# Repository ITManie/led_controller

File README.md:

# 

Arduino project to control RGB LED strip

## Part list
 - IQRF Development set [IQRF DS-START-04](http://eshop.iqrf.org/products/detail/DS-START-04)
 - IQRF Breakout board [IQRF BB-01](http://eshop.iqrf.org/products/detail/IQRF-BB-01)
 - IQRF gateway (for example [IQRF GW-ETH-02A](http://eshop.iqrf.org/products/detail/GW-ETH-02A%2872D%29))
 - Atmel MCU with Arduino firmware or Adruino (for example [Arduino Nano](http://www.tme.eu/en/details/a000005/arduino-development-kits/arduino/arduino-nano/))
 - 3x [STMicroelectronics TIP122](http://www.tme.eu/en/details/tip122/npn-tht-darlington-transistors/st-microelectronics/)
 - 5V voltage stabiliser (for example [ON Semiconductor MC78M05CTG](http://www.tme.eu/en/details/mc78m05ctg/unregulated-voltage-regulators/on-semiconductor/))
 - RGB LED strip (for example [OptoFlash OPRGB5060-6012B](http://www.tme.eu/en/details/oprgb5060-6012b/light-sources-led-ribbon/optoflash/))
 - 5,5/2,1mm DC jack (for example [CLIFF FC68148](http://www.tme.eu/en/details/fc68148/dc-power-connectors/cliff/))
 - 12V power supply (for example [ESPE ZSIDT12/3A](http://www.tme.eu/en/details/zsidt12_3a/mains-power-supplies/espe/))
 - terminal block PCB mount (for example [Degson Electronics DG300-5.0-02P-12-00A(H)](http://www.tme.eu/en/details/dg300-5.0-2p12/terminal-blocks-pcb-mount/degson-electronics/dg300-50-02p-12-00ah/))

## Arduino libraries

 * [IQRF](https://github.com/iqrfsdk/clibiqrf-arduino)
 * [MsTimer2](https://github.com/PaulStoffregen/MsTimer2)

## Packets

### Ping
<table>
<tr>
<th>0-FF</th>
<th>100-1FF</th>
<th>200-2FF</th>
<th>300-3FF</th>
<th>400-4FF</th>
<th>500-5FF</th>
</tr>
<tr>
<td>version</td>
<td>type</td>
<td colspan="4">address</td>
</tr>
<tr>
<td>0</td>
<td>0</td>
<td>0-FF</td>
<td>0-FF</td>
<td>0-FF</td>
<td>0-FF</td>
</tr>
</table>

### Pong
<table>
<tr>
<th>0-FF</th>
<th>100-1FF</th>
<th>200-2FF</th>
<th>300-3FF</th>
<th>400-4FF</th>
<th>500-5FF</th>
</tr>
<tr>
<td>version</td>
<td>type</td>
<td colspan="4">address</td>
</tr>
<tr>
<td>0</td>
<td>1</td>
<td>0-FF</td>
<td>0-FF</td>
<td>0-FF</td>
<td>0-FF</td>
</tr>
</table>

### Set color
<table>
<tr>
<th>00-FF</th>
<th>100-1FF</th>
<th>200-2FF</th>
<th>300-3FF</th>
<th>400-4FF</th>
<th>500-5FF</th>
<th>600-6FF</th>
<th>700-7FF</th>
<th>800-8FF</th>
<th>900-9FF</th>
</tr>
<tr>
<td>version</td>
<td>type</td>
<td colspan="4">address</td>
<td>red</td>
<td>green</td>
<td>blue</td>
<td>alpha</td>
</tr>
<tr>
<td>0</td>
<td>2</td>
<td>0-FF</td>
<td>0-FF</td>
<td>0-FF</td>
<td>0-FF</td>
<td>0-FF</td>
<td>0-FF</td>
<td>0-FF</td>
<td>0-1</td>
</tr>
</table>

## Schema
### Prototype

### Production

## License
led-controller is licensed under the GPLv3 license:

 > Copyright (C) 2016 Roman Ondráček
 > 
 > This program is free software: you can redistribute it and/or modify
 > it under the terms of the GNU General Public License as published by
 > the Free Software Foundation, either version 3 of the License, or
 > (at your option) any later version.
 > 
 > This program is distributed in the hope that it will be useful,
 > but WITHOUT ANY WARRANTY; without even the implied warranty of
 > MERCHANTABILITY or FITNESS FOR A PARTICULAR PURPOSE.  See the
 > GNU General Public License for more details.
 > 
 > You should have received a copy of the GNU General Public License
 > along with this program.  If not, see <http://www.gnu.org/licenses/>.

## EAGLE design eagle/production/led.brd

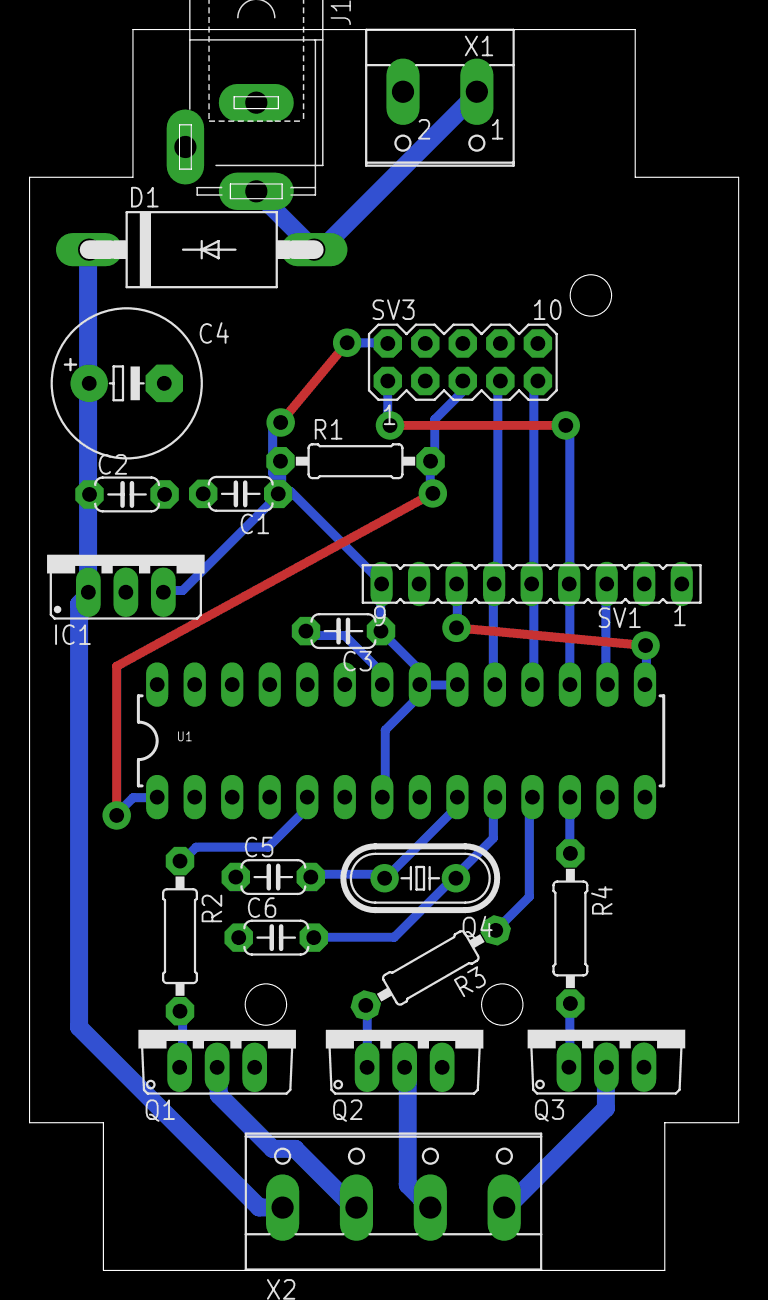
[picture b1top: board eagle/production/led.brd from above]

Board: 2 copper layers, 48.0 x 84.0 mm, 22 parts (0 on the bottom side), 21 nets.

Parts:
C1, C2, C3: 100n; C050-024X044
C4: 470u; E5-10,5
C5, C6: 18p; C050-024X044
D1: BY550; DO27-15
IC1: 78XXS
J1: SPC4078
Q1, Q2, Q3: TIP120; TO220AV
Q4: 16MHz; HC49/S
R1: 10k; 0207/10
R2, R3, R4: 1k; 0207/10
SV1: FE09
SV3: MA05-2
U1: ATMEGA328P_PDIP; DIL28-3
X1: W237-102
X2: W237-4

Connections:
+5V: C1.1, C3.1, IC1.OUT, R1.1, SV1.9, SV3.2, U1.7, U1.20, U1.21
+12V: C2.1, C4.+, D1.C, IC1.IN, X2.1
GND: C1.2, C2.2, C3.2, C4.-, C5.1, C6.1, IC1.GND, J1.1, J1.2, Q1.E, Q2.E, Q3.E, SV1.8, SV3.4, SV3.6, SV3.8, SV3.10, U1.8, U1.22, X1.2
unnamed: Q3.C, X2.4
unnamed: SV1.5, SV3.9, U1.18
unnamed: D1.A, J1.3, X1.1
unnamed: Q1.B, R2.2
unnamed: R1.2, SV3.5, U1.1
unnamed: SV1.4, SV3.1, U1.17
unnamed: SV1.3, U1.16
unnamed: SV1.7, U1.15
unnamed: Q2.C, X2.3
unnamed: Q1.C, X2.2
unnamed: R4.1, U1.12
unnamed: R3.1, U1.11
unnamed: R2.1, U1.5
unnamed: SV1.6, SV3.7, U1.19
unnamed: Q2.B, R3.2
unnamed: Q3.B, R4.2
S$1: C6.2, Q4.1, U1.10
S$2: C5.2, Q4.2, U1.9

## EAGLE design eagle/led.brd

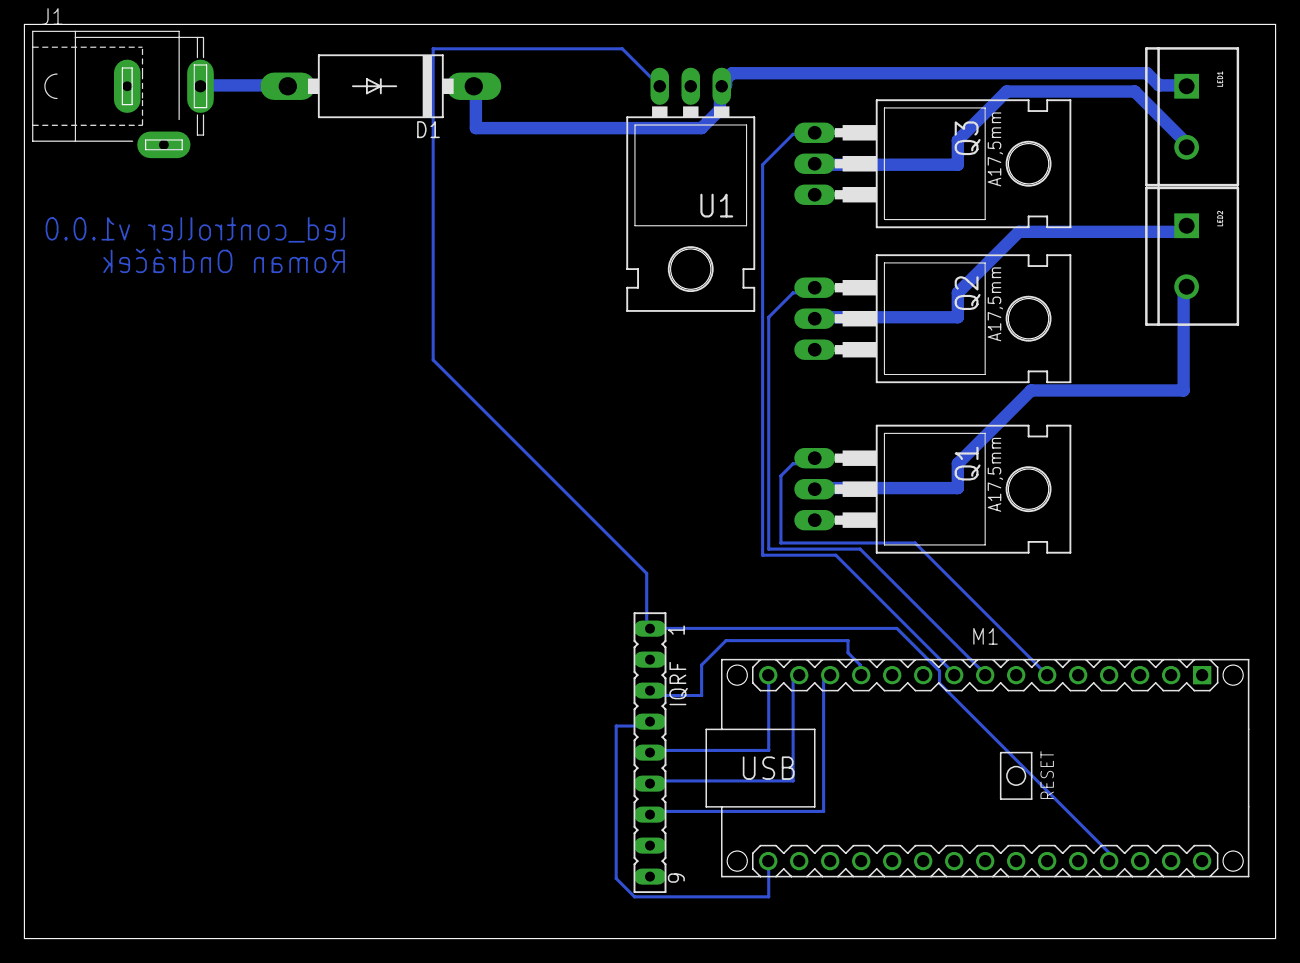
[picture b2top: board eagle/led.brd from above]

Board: 2 copper layers, 102.5 x 74.9 mm, 10 parts (0 on the bottom side), 15 nets.

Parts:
D1: BY550; DO27-15
IQRF: FE09
J1: 12V/3A; SPC4077
LED1, LED2: SCREWTERMINAL-5MM-2
M1: ARDUINO-NANO-3.0
Q1, Q2, Q3: TIP120; TO220AH
U1: MC78M05CT; TO-220-ALT

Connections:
+5V: IQRF.1, M1.J2.4, U1.OUT
+12V: D1.C, LED1.1, U1.IN
GND: IQRF.2, J1.1, J1.2, M1.J1.4, M1.J2.2, Q1.E, Q2.E, Q3.E, U1.GND
unnamed: D1.A, J1.3
unnamed: M1.J1.6, Q1.B
unnamed: M1.J1.8, Q2.B
unnamed: M1.J1.9, Q3.B
unnamed: LED1.2, Q3.C
unnamed: LED2.1, Q2.C
unnamed: LED2.2, Q1.C
unnamed: IQRF.4, M1.J2.15
unnamed: IQRF.3, M1.J1.12
unnamed: IQRF.5, M1.J1.15
unnamed: IQRF.6, M1.J1.14
unnamed: IQRF.7, M1.J1.13

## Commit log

2016-01-31 Added Read me
2016-01-31 Added Travis CI configuration
2016-01-31 Added Arduino project source code
2016-01-31 Added Platform.io config
2016-01-31 Added MsTimer2 library for platform.io
2016-01-31 Edit Travis CI configuration
2016-01-31 Fix syntax error in Arduino sources
2016-01-31 Fix other syntax error in Arduino project
2016-02-01 Added libraries to Read me and delete libraries from src dir
2016-02-01 Update Plarform.io config
2016-02-01 Replace library MsTimer2 files to platformio installation
2016-02-01 Add IQRF lib register
2016-02-01 Added TODO
2016-02-01 Added libraries to sketch
2016-02-02 Replace IQRF library files to platformio installation
2016-02-02 Rename src to arduino, rename repository
2016-02-02 Edited Read me
2016-02-02 Added tested boards
2016-02-02 Remove problematic boards
2016-02-03 Added schematic and RGB LED pins
2016-02-03 Added shitty implementation of reading numbers from buffer for PWM regulation RGB LEDs
2016-02-04 Added debug informations
2016-02-04 Added skeleton for app powered by Apache Cordova
2016-02-07 Added drone.io build status
2016-02-07 Added wercker configuration
2016-02-07 Added wercker status
2016-02-07 Fix wercker configuration
2016-02-07 Fix platformio config
2016-02-07 Added GPLv3 badge
2016-02-09 Added packet structure
2016-02-10 Add Gitter badge
2016-02-10 Added Gitter badge
2016-02-10 Added sending notificatoins from Travis CI to Gitter
2016-02-10 Added implementation of setcolor packet
2016-02-19 Edited protocol diagrams
2016-02-19 Clean code
2016-02-19 Repair Travis CI configuration
2016-02-20 Added function to send pong
2016-02-20 Finished implementation of protocol
2016-02-21 Added comments to Arduino code
2016-02-21 Edit schematics in Arduino code
2016-02-23 Set LED pins as outputs
2016-02-23 Repair pinMode
2016-02-26 Added Nette skeleton for webapp
2016-03-14 [eagle] Added schematic and PCB design
2016-03-15 [Eagle] Create new board
2016-03-15 [Eagle] Update board
2016-03-16 [Eagle] Added schematic and board in pictures
2016-03-24 [Arduino] Redefine LED pins
2016-03-25 [IQRF] Added software for IQRF
2016-03-26 [README] Update name of repository
2016-03-26 [Travis CI] Remove unnecessary boards
2016-03-28 [Docs] Added skeleton of documentation for MCU letí
2016-03-28 [Wercker CI] Remove unnecessary boards
2016-03-30 [Arduino] Fix IQRF module detection
2016-03-30 [IQRF] Update sotfware for IQRF module
2016-03-31 [Arduino] Added debug infos
2016-04-13 [LICENSE] Added license header to Arduino and IQRF source code
2016-04-16 [Eagle] New schematic
2016-04-16 [Arduino] Added function to set color of RGB LED strip
2016-04-16 [webapp] Added Netbeans files to .gitignore
2016-04-17 [Docs] Changed font color from red to black
2016-04-17 [Webapp] Code format
2016-04-20 [IQRF] Update IQRF firmware
2016-04-22 [IQRF] Repaired firmware for IQRF RF module
2016-04-22 [Eagle] Added board
2016-04-24 [README] Added license
2016-04-24 [README] Added part list
2016-04-24 [README] Added schema
2016-04-24 [README] Added logo
2016-04-24 [docs] Added some informations to MCU letí 2016 ducumentation
2016-04-26 [webapp] Update dependencies
2016-04-28 [docs] Update documentation to contest MCUletí 2016
2016-04-29 [README] Update Read me (flat icon and update part list)
2016-04-29 [git] Update .gitignore
2016-04-29 [docs] Added infos about selected MCU
2016-04-29 [docs] Added some info about selected wireless module
2016-04-29 [docs] Update documentation
2016-04-30 [docs] Updated documantation
2016-04-30 [docs] Final version of documentation
2016-04-30 [docs] Added documantition in PDF format
2016-04-30 [Wercker CI] Remove configuration
2016-04-30 [Arduino] Fix bracket in condition
2016-05-04 [webapp] Update Nette framework to version 2.4
2016-05-04 [webapp] Remove adminer
2016-05-04 [webapp] Added IQRF extension to config
2016-05-05 [Eagle] Delete information file
2016-05-13 [Arduino] Clean code
2016-05-13 [Eagle] Moved prototype schema to own directory
2016-05-19 Added icon for project
2016-05-19 Formated code of SVG code of logo
2016-05-19 [GitLab CI] Added tests for Arduino code
2016-05-20 Added presentation for IQRF Contest
2016-05-20 Fixed typos in presentation
2016-05-20 Fixed other typos in presentation
2016-05-22 Added final board and schema
2016-05-22 [Eagle] Board repaired
2016-05-24 [Eagle] Edited schema and board
2016-05-24 [Eagle] Added capacitors and resistors
2016-05-25 Updated presentation in Enlish and added presentation in Czech
2016-05-25 Used official library for Arduino
2016-05-26 Fixed mirroing of PCB
2016-05-26 Fixed PCB
2016-05-26 Udated links in Read Me
2016-05-30 [Eagle] Fixed board
2016-06-02 Updated schema and board
2016-06-05 Added board to print
2016-06-08 [Arduino] Refactored source code
2016-06-08 Updated documentation to contest MCU letí 2016
2016-06-10 [Docs] Fixed grammar in documentation to MCU letí contest
2016-06-10 [Docs] Updated presentation iv Czech
2016-06-10 [Eagle] Added board and edited schema
2016-08-03 Fixed Arduino sources
2016-11-12 Remove web application from this repository
2016-11-12 Renamed eagle files
2016-11-13 Add EDA's files for version 2.0

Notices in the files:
parts and their libraries:
SparkFun-Connectors: Licensing: Creative Commons ShareAlike 4.0 International - https://creativecommons.org/licenses/by-sa/4.0
diy-modules: Released under the Creative Commons Attribution 4.0 International License: http://creativecommons.org/licenses/by/4.0
